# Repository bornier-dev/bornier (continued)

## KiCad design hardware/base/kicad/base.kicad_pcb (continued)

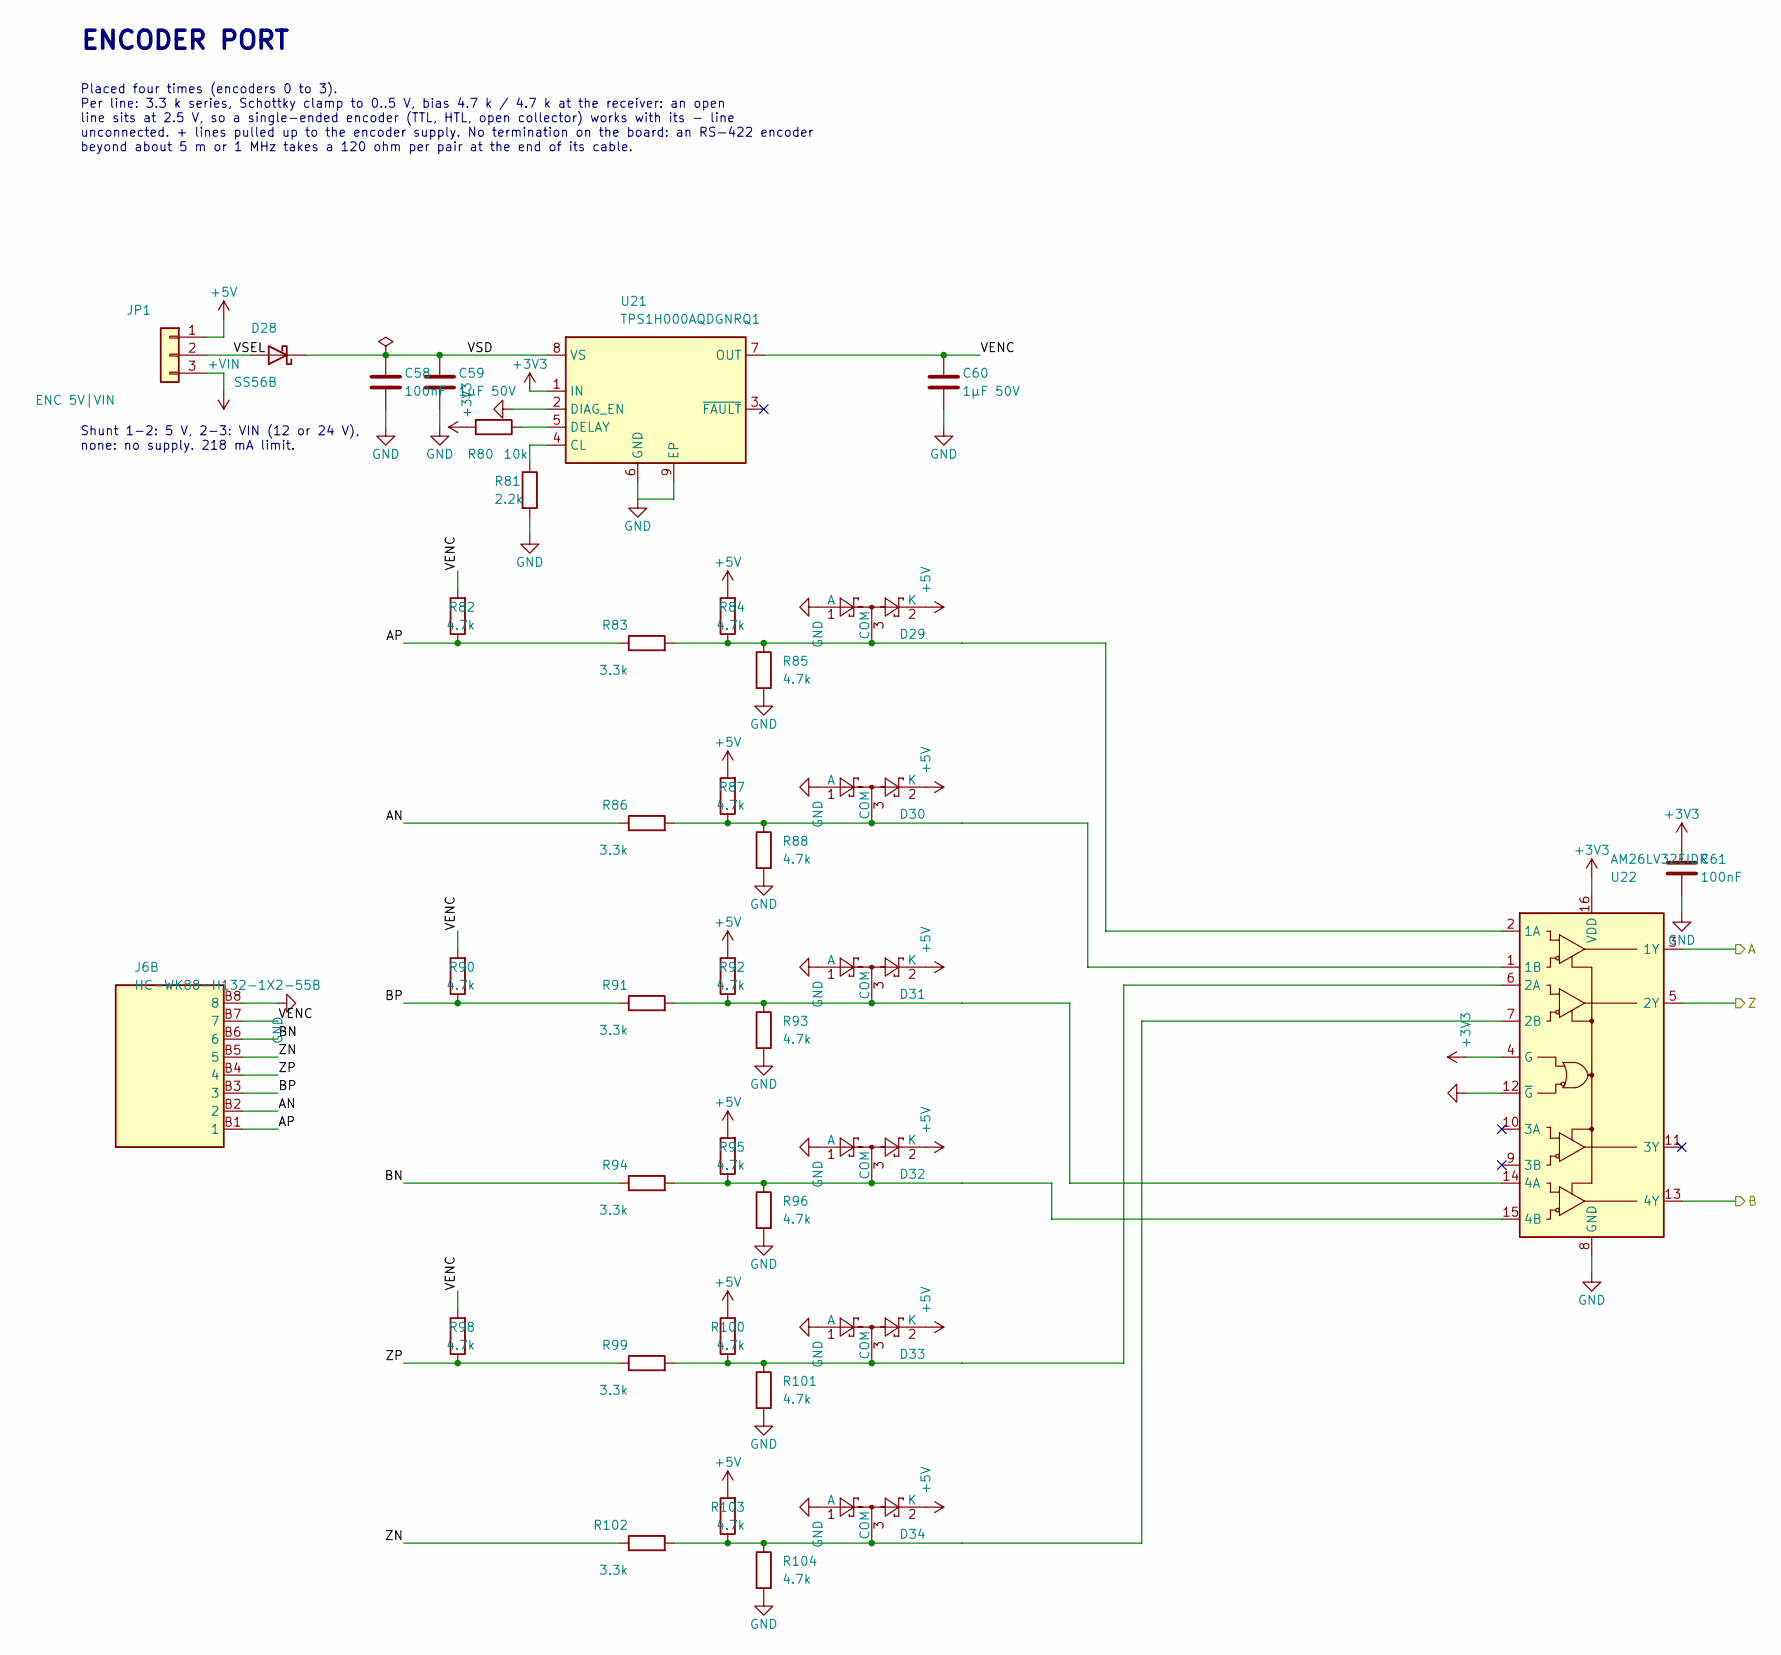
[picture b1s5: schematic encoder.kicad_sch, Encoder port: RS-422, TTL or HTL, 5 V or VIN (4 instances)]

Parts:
C58, C61: 100nF; C_0402_1005Metric; LCSC C307331
C59, C60: 1µF 50V; C_0603_1608Metric; LCSC C15849
D28: SS56B; D_SMB; LCSC C14651
D29, D30, D31, D32, D33, D34: BAT54S; SOT-23; LCSC C12765
J6: HC-WK88-H132-1X2-55B; RJ45x2_HongCheng_HC-WK88-H132-1X2-55B; LCSC C7501828
JP1: ENC 5V|VIN; PinHeader_1x03_P2.54mm_Vertical; LCSC C2937625
R80: 10k; R_0402_1005Metric; LCSC C25744
R81: 2.2k; R_0402_1005Metric; LCSC C25879
R82, R90, R98: 4.7k; R_1206_3216Metric; LCSC C17936
R83, R86, R91, R94, R99, R102: 3.3k; R_1206_3216Metric; LCSC C26032
R84, R85, R87, R88, R92, R93, R95, R96, R100, R101, R103, R104: 4.7k; R_0402_1005Metric; LCSC C25900
U21: TPS1H000AQDGNRQ1; HVSSOP-8-1EP_3x3mm_P0.65mm_EP1.57x1.89mm; LCSC C2653764
U22: AM26LV32EIDR; SOIC-16_3.9x9.9mm_P1.27mm; LCSC C527448

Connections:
+3V3: C61.1, R80.2, U21.1 (IN), U22.4 (G), U22.16 (VDD); also elsewhere on the board
+5V: D29.2 (K), D30.2 (K), D31.2 (K), D32.2 (K), D33.2 (K), D34.2 (K), JP1.1, R84.2, R87.2, R92.2, R95.2, R100.2, R103.2; also elsewhere on the board
+VIN: JP1.3; also elsewhere on the board
/Encoder 0/AN: J6.B2 (2), R86.1
/Encoder 0/AP: J6.B1 (1), R82.1, R83.1
/Encoder 0/BN: J6.B6 (6), R94.1
/Encoder 0/BP: J6.B3 (3), R90.1, R91.1
/Encoder 0/VENC: C60.1, J6.B7 (7), R82.2, R90.2, R98.2, U21.7 (OUT)
/Encoder 0/VSD: C58.1, C59.1, D28.1 (K), U21.8 (VS)
/Encoder 0/VSEL: D28.2 (A), JP1.2
/Encoder 0/ZN: J6.B5 (5), R102.1
/Encoder 0/ZP: J6.B4 (4), R98.1, R99.1
ENC0_A: U22.3 (1Y); also elsewhere on the board
ENC0_B: U22.13 (4Y); also elsewhere on the board
ENC0_Z: U22.5 (2Y); also elsewhere on the board
GND: C58.2, C59.2, C60.2, C61.2, D29.1 (A), D30.1 (A), D31.1 (A), D32.1 (A), D33.1 (A), D34.1 (A), J6.B8 (8), R81.2, R85.2, R88.2, R93.2, R96.2, R101.2, R104.2, U21.2 (DIAG_EN), U21.6 (GND), U21.9 (EP), U22.8 (GND), U22.12 (~G); also elsewhere on the board
unnamed: D29.3 (COM), R83.2, R84.1, R85.1, U22.2 (1A)
unnamed: D30.3 (COM), R86.2, R87.1, R88.1, U22.1 (1B)
unnamed: D31.3 (COM), R91.2, R92.1, R93.1, U22.14 (4A)
unnamed: D32.3 (COM), R94.2, R95.1, R96.1, U22.15 (4B)
unnamed: D33.3 (COM), R99.2, R100.1, R101.1, U22.6 (2A)
unnamed: D34.3 (COM), R102.2, R103.1, R104.1, U22.7 (2B)
unnamed: R81.1, U21.4 (CL)
unnamed: R80.1, U21.5 (DELAY)

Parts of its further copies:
C62, C65, C66, C69, C70, C73: 100nF; C_0402_1005Metric; LCSC C307331
C63, C64, C67, C68, C71, C72: 1µF 50V; C_0603_1608Metric; LCSC C15849
D35, D42, D49: SS56B; D_SMB; LCSC C14651
D36, D37, D38, D39, D40, D41, D43, D44, D45, D46, D47, D48, D50, D51, D52, D53, D54, D55: BAT54S; SOT-23; LCSC C12765
J7, J8, J9: HC-WK88-H132-1X2-55B; RJ45x2_HongCheng_HC-WK88-H132-1X2-55B; LCSC C7501828
JP2, JP3, JP4: ENC 5V|VIN; PinHeader_1x03_P2.54mm_Vertical; LCSC C2937625
R106, R132, R158: 10k; R_0402_1005Metric; LCSC C25744
R107, R133, R159: 2.2k; R_0402_1005Metric; LCSC C25879
R108, R116, R124, R134, R142, R150, R160, R168, R176: 4.7k; R_1206_3216Metric; LCSC C17936
R109, R112, R117, R120, R125, R128, R135, R138, R143, R146, R151, R154, R161, R164, R169, R172, R177, R180: 3.3k; R_1206_3216Metric; LCSC C26032
R110, R111, R113, R114, R118, R119, R121, R122, R126, R127, R129, R130, R136, R137, R139, R140, R144, R145, R147, R148, R152, R153, R155, R156, R162, R163, R165, R166, R170, R171, R173, R174, R178, R179, R181, R182: 4.7k; R_0402_1005Metric; LCSC C25900
U23, U25, U27: TPS1H000AQDGNRQ1; HVSSOP-8-1EP_3x3mm_P0.65mm_EP1.57x1.89mm; LCSC C2653764
U24, U26, U28: AM26LV32EIDR; SOIC-16_3.9x9.9mm_P1.27mm; LCSC C527448

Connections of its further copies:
+3V3: C65.1, C69.1, C73.1, R106.2, R132.2, R158.2, U23.1 (IN), U24.4 (G), U24.16 (VDD), U25.1 (IN), U26.4 (G), U26.16 (VDD), U27.1 (IN), U28.4 (G), U28.16 (VDD); also elsewhere on the board
+5V: D36.2 (K), D37.2 (K), D38.2 (K), D39.2 (K), D40.2 (K), D41.2 (K), D43.2 (K), D44.2 (K), D45.2 (K), D46.2 (K), D47.2 (K), D48.2 (K), D50.2 (K), D51.2 (K), D52.2 (K), D53.2 (K), D54.2 (K), D55.2 (K), JP2.1, JP3.1, JP4.1, R110.2, R113.2, R118.2, R121.2, R126.2, R129.2, R136.2, R139.2, R144.2, R147.2, R152.2, R155.2, R162.2, R165.2, R170.2, R173.2, R178.2, R181.2; also elsewhere on the board
+VIN: JP2.3, JP3.3, JP4.3; also elsewhere on the board
+VIN_OUT: J7.A7 (7), J8.A7 (7), J9.A7 (7); also elsewhere on the board
/Drive 1/ALM_IN: J7.A5 (5); also elsewhere on the board
/Drive 1/DIR_N: J7.A6 (6); also elsewhere on the board
/Drive 1/DIR_P: J7.A3 (3); also elsewhere on the board
/Drive 1/ENA_OUT: J7.A4 (4); also elsewhere on the board
/Drive 1/STEP_N: J7.A2 (2); also elsewhere on the board
/Drive 1/STEP_P: J7.A1 (1); also elsewhere on the board
/Drive 2/ALM_IN: J8.A5 (5); also elsewhere on the board
/Drive 2/DIR_N: J8.A6 (6); also elsewhere on the board
/Drive 2/DIR_P: J8.A3 (3); also elsewhere on the board
/Drive 2/ENA_OUT: J8.A4 (4); also elsewhere on the board
/Drive 2/STEP_N: J8.A2 (2); also elsewhere on the board
/Drive 2/STEP_P: J8.A1 (1); also elsewhere on the board
/Drive 3/ALM_IN: J9.A5 (5); also elsewhere on the board
/Drive 3/DIR_N: J9.A6 (6); also elsewhere on the board
/Drive 3/DIR_P: J9.A3 (3); also elsewhere on the board
/Drive 3/ENA_OUT: J9.A4 (4); also elsewhere on the board
/Drive 3/STEP_N: J9.A2 (2); also elsewhere on the board
/Drive 3/STEP_P: J9.A1 (1); also elsewhere on the board
/Encoder 1/AN: J7.B2 (2), R112.1
/Encoder 1/AP: J7.B1 (1), R108.1, R109.1
/Encoder 1/BN: J7.B6 (6), R120.1
/Encoder 1/BP: J7.B3 (3), R116.1, R117.1
/Encoder 1/VENC: C64.1, J7.B7 (7), R108.2, R116.2, R124.2, U23.7 (OUT)
/Encoder 1/VSD: C62.1, C63.1, D35.1 (K), U23.8 (VS)
/Encoder 1/VSEL: D35.2 (A), JP2.2
/Encoder 1/ZN: J7.B5 (5), R128.1
/Encoder 1/ZP: J7.B4 (4), R124.1, R125.1
/Encoder 2/AN: J8.B2 (2), R138.1
/Encoder 2/AP: J8.B1 (1), R134.1, R135.1
/Encoder 2/BN: J8.B6 (6), R146.1
/Encoder 2/BP: J8.B3 (3), R142.1, R143.1
/Encoder 2/VENC: C68.1, J8.B7 (7), R134.2, R142.2, R150.2, U25.7 (OUT)
/Encoder 2/VSD: C66.1, C67.1, D42.1 (K), U25.8 (VS)
/Encoder 2/VSEL: D42.2 (A), JP3.2
/Encoder 2/ZN: J8.B5 (5), R154.1
/Encoder 2/ZP: J8.B4 (4), R150.1, R151.1
/Encoder 3/AN: J9.B2 (2), R164.1
/Encoder 3/AP: J9.B1 (1), R160.1, R161.1
/Encoder 3/BN: J9.B6 (6), R172.1
/Encoder 3/BP: J9.B3 (3), R168.1, R169.1
/Encoder 3/VENC: C72.1, J9.B7 (7), R160.2, R168.2, R176.2, U27.7 (OUT)
/Encoder 3/VSD: C70.1, C71.1, D49.1 (K), U27.8 (VS)
/Encoder 3/VSEL: D49.2 (A), JP4.2
/Encoder 3/ZN: J9.B5 (5), R180.1
/Encoder 3/ZP: J9.B4 (4), R176.1, R177.1
CHASSIS: J7.SH, J8.SH, J9.SH; also elsewhere on the board
ENC1_A: U24.3 (1Y); also elsewhere on the board
ENC1_B: U24.13 (4Y); also elsewhere on the board
ENC1_Z: U24.5 (2Y); also elsewhere on the board
ENC2_A: U26.3 (1Y); also elsewhere on the board
ENC2_B: U26.13 (4Y); also elsewhere on the board
ENC2_Z: U26.5 (2Y); also elsewhere on the board
ENC3_A: U28.3 (1Y); also elsewhere on the board
ENC3_B: U28.13 (4Y); also elsewhere on the board
ENC3_Z: U28.5 (2Y); also elsewhere on the board
GND: C62.2, C63.2, C64.2, C65.2, C66.2, C67.2, C68.2, C69.2, C70.2, C71.2, C72.2, C73.2, D36.1 (A), D37.1 (A), D38.1 (A), D39.1 (A), D40.1 (A), D41.1 (A), D43.1 (A), D44.1 (A), D45.1 (A), D46.1 (A), D47.1 (A), D48.1 (A), D50.1 (A), D51.1 (A), D52.1 (A), D53.1 (A), D54.1 (A), D55.1 (A), J7.A8 (8), J7.B8 (8), J8.A8 (8), J8.B8 (8), J9.A8 (8), J9.B8 (8), R107.2, R111.2, R114.2, R119.2, R122.2, R127.2, R130.2, R133.2, R137.2, R140.2, R145.2, R148.2, R153.2, R156.2, R159.2, R163.2, R166.2, R171.2, R174.2, R179.2, R182.2, U23.2 (DIAG_EN), U23.6 (GND), U23.9 (EP), U24.8 (GND), U24.12 (~G), U25.2 (DIAG_EN), U25.6 (GND), U25.9 (EP), U26.8 (GND), U26.12 (~G), U27.2 (DIAG_EN), U27.6 (GND), U27.9 (EP), U28.8 (GND), U28.12 (~G); also elsewhere on the board
unnamed: D36.3 (COM), R109.2, R110.1, R111.1, U24.2 (1A)
unnamed: D37.3 (COM), R112.2, R113.1, R114.1, U24.1 (1B)
unnamed: D38.3 (COM), R117.2, R118.1, R119.1, U24.14 (4A)
unnamed: D39.3 (COM), R120.2, R121.1, R122.1, U24.15 (4B)
unnamed: D40.3 (COM), R125.2, R126.1, R127.1, U24.6 (2A)
unnamed: D41.3 (COM), R128.2, R129.1, R130.1, U24.7 (2B)
unnamed: D43.3 (COM), R135.2, R136.1, R137.1, U26.2 (1A)
unnamed: D44.3 (COM), R138.2, R139.1, R140.1, U26.1 (1B)
unnamed: D45.3 (COM), R143.2, R144.1, R145.1, U26.14 (4A)
unnamed: D46.3 (COM), R146.2, R147.1, R148.1, U26.15 (4B)
unnamed: D47.3 (COM), R151.2, R152.1, R153.1, U26.6 (2A)
unnamed: D48.3 (COM), R154.2, R155.1, R156.1, U26.7 (2B)
unnamed: D50.3 (COM), R161.2, R162.1, R163.1, U28.2 (1A)
unnamed: D51.3 (COM), R164.2, R165.1, R166.1, U28.1 (1B)
unnamed: D52.3 (COM), R169.2, R170.1, R171.1, U28.14 (4A)
unnamed: D53.3 (COM), R172.2, R173.1, R174.1, U28.15 (4B)
unnamed: D54.3 (COM), R177.2, R178.1, R179.1, U28.6 (2A)
unnamed: D55.3 (COM), R180.2, R181.1, R182.1, U28.7 (2B)
unnamed: R107.1, U23.4 (CL)
unnamed: R106.1, U23.5 (DELAY)
unnamed: R133.1, U25.4 (CL)
unnamed: R132.1, U25.5 (DELAY)
unnamed: R159.1, U27.4 (CL)
unnamed: R158.1, U27.5 (DELAY)

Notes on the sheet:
ENCODER PORT
Placed four times (encoders 0 to 3). Per line: 3.3 k series, Schottky clamp to 0..5 V, bias 4.7 k / 4.7 k at the receiver: an open line sits at 2.5 V, so a single-ended encoder (TTL, HTL, open collector) works with its - line unconnected. + lines pulled up to the encoder supply. No termination on t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
Shunt 1-2: 5 V, 2-3: VIN (12 or 24 V), none: no supply. 218 mA limit.

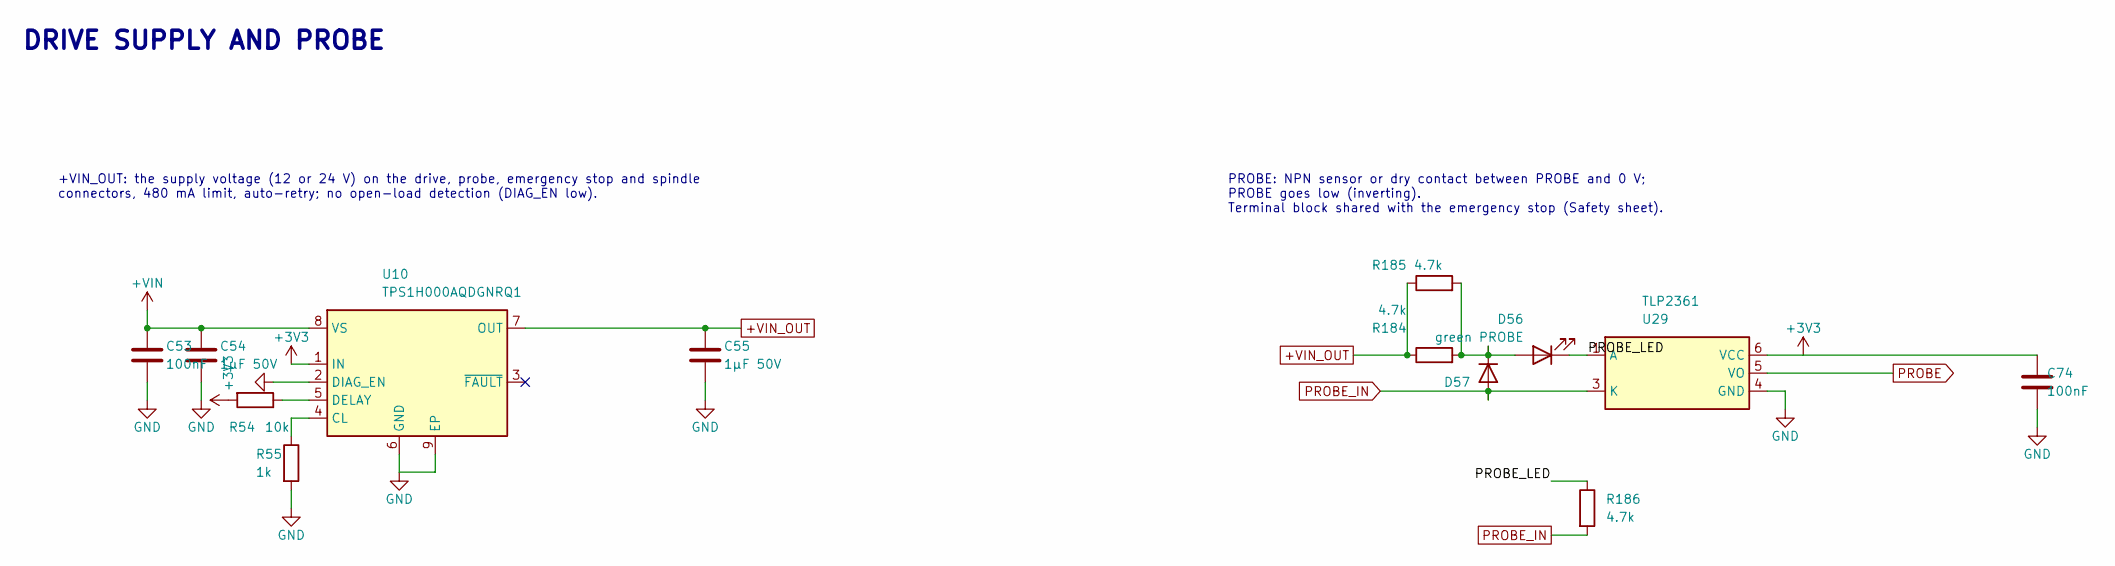
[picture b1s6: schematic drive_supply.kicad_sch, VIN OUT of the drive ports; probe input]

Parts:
C53, C74: 100nF; C_0402_1005Metric; LCSC C307331
C54, C55: 1µF 50V; C_0603_1608Metric; LCSC C15849
D56: green PROBE; LED_0603_1608Metric; LCSC C2289
D57: 1N4148WS; D_SOD-323; LCSC C2128
R54: 10k; R_0402_1005Metric; LCSC C25744
R55: 1k; R_0402_1005Metric; LCSC C11702
R184, R185: 4.7k; R_1206_3216Metric; LCSC C17936
R186: 4.7k; R_0402_1005Metric; LCSC C25900
U10: TPS1H000AQDGNRQ1; HVSSOP-8-1EP_3x3mm_P0.65mm_EP1.57x1.89mm; LCSC C2653764
U29: TLP2361; SO-5-6_4.55x3.7mm_P1.27mm; LCSC C107626

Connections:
+3V3: C74.1, R54.2, U10.1 (IN), U29.6 (VCC); also elsewhere on the board
+VIN: C53.1, C54.1, U10.8 (VS); also elsewhere on the board
+VIN_OUT: C55.1, R184.1, R185.1, U10.7 (OUT); also elsewhere on the board
/Drive supply and probe/PROBE_LED: D56.1 (K), R186.1, U29.1 (A)
GND: C53.2, C54.2, C55.2, C74.2, R55.2, U10.2 (DIAG_EN), U10.6 (GND), U10.9 (EP), U29.4 (GND); also elsewhere on the board
unnamed: D56.2 (A), D57.1 (K), R184.2, R185.2
unnamed: R55.1, U10.4 (CL)
unnamed: R54.1, U10.5 (DELAY)
PROBE: U29.5 (VO); also elsewhere on the board
PROBE_IN: D57.2 (A), R186.2, U29.3 (K); also elsewhere on the board

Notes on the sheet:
DRIVE SUPPLY AND PROBE
+VIN_OUT: the supply voltage (12 or 24 V) on the drive, probe, emergency stop and spindle connectors, 480 mA limit, auto-retry; no open-load detection (DIAG_EN low).
PROBE: NPN sensor or dry contact between PROBE and 0 V; PROBE goes low (inverting). Terminal block shared with the emergency stop (Safety sheet).

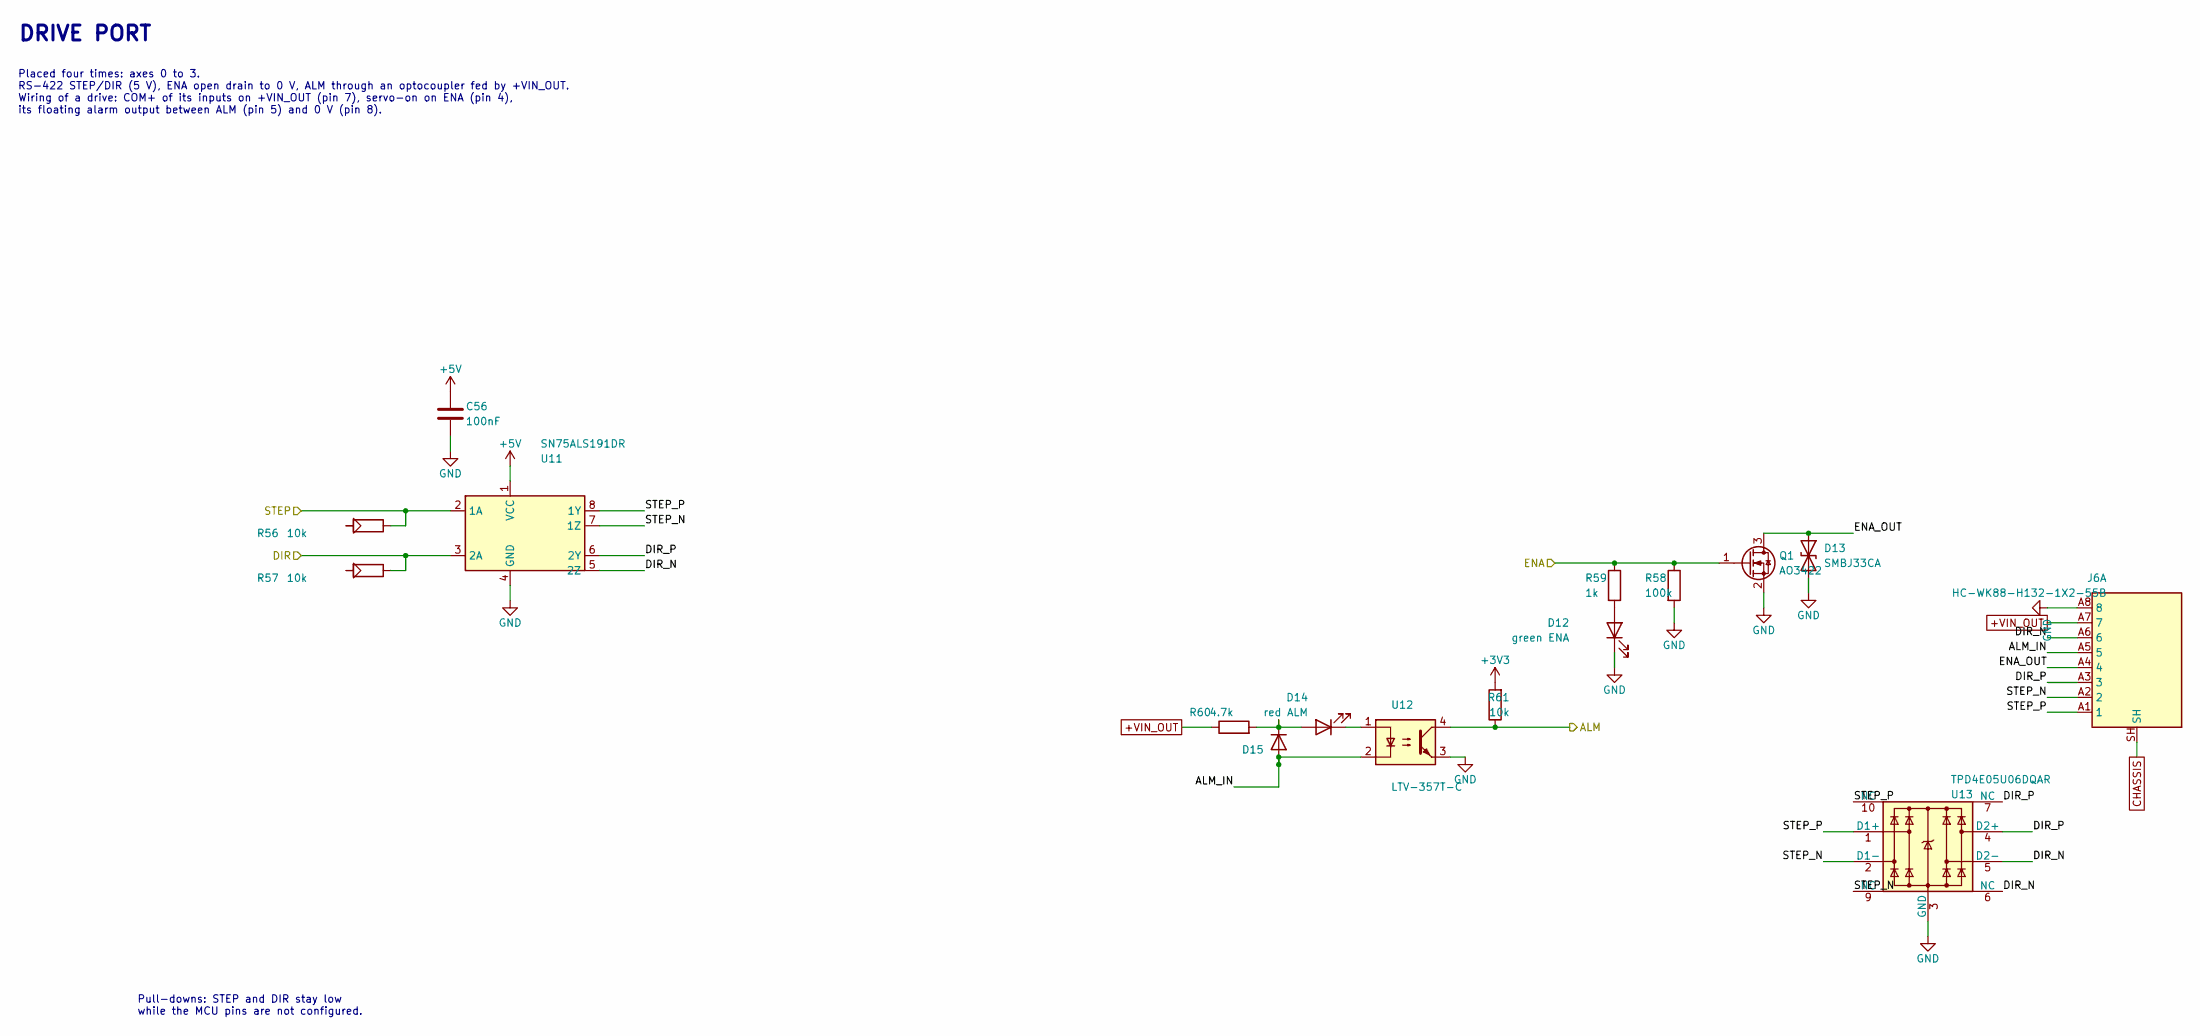
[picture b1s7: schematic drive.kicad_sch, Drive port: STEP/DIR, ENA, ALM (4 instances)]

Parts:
C56: 100nF; C_0402_1005Metric; LCSC C307331
D12: green ENA; LED_0603_1608Metric; LCSC C2289
D13: SMBJ33CA; D_SMB; LCSC C78420
D14: red ALM; LED_0603_1608Metric; LCSC C2286
D15: 1N4148WS; D_SOD-323; LCSC C2128
J6: HC-WK88-H132-1X2-55B; RJ45x2_HongCheng_HC-WK88-H132-1X2-55B; LCSC C7501828
Q1: AO3422; SOT-23; LCSC C37130
R56, R57, R61: 10k; R_0402_1005Metric; LCSC C25744
R58: 100k; R_0402_1005Metric; LCSC C25741
R59: 1k; R_0402_1005Metric; LCSC C11702
R60: 4.7k; R_1206_3216Metric; LCSC C17936
U11: SN75ALS191DR; SOIC-8_3.9x4.9mm_P1.27mm; LCSC C2871261
U12: LTV-357T-C; SO-4_4.4x3.6mm_P2.54mm; LCSC C119091
U13: TPD4E05U06DQAR; USON-10_2.5x1.0mm_P0.5mm; LCSC C138714

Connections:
+3V3: R61.2; also elsewhere on the board
+5V: C56.1, U11.1 (VCC); also elsewhere on the board
+VIN_OUT: J6.A7 (7), R60.1; also elsewhere on the board
/Drive 0/ALM_IN: D15.2 (A), J6.A5 (5), U12.2
/Drive 0/DIR_N: J6.A6 (6), U11.5 (2Z), U13.5 (D2-), U13.6 (NC)
/Drive 0/DIR_P: J6.A3 (3), U11.6 (2Y), U13.4 (D2+), U13.7 (NC)
/Drive 0/ENA_OUT: D13.1 (A1), J6.A4 (4), Q1.3 (D)
/Drive 0/STEP_N: J6.A2 (2), U11.7 (1Z), U13.2 (D1-), U13.9 (NC)
/Drive 0/STEP_P: J6.A1 (1), U11.8 (1Y), U13.1 (D1+), U13.10 (NC)
ALM0: R61.1, U12.4; also elsewhere on the board
CHASSIS: J6.SH; also elsewhere on the board
DIR0: R57.1, U11.3 (2A); also elsewhere on the board
ENA0: Q1.1 (G), R58.1, R59.1; also elsewhere on the board
GND: C56.2, D12.1 (K), D13.2 (A2), J6.A8 (8), Q1.2 (S), R56.2, R57.2, R58.2, U11.4 (GND), U12.3, U13.3 (GND), U13.8 (GND); also elsewhere on the board
unnamed: D12.2 (A), R59.2
unnamed: D14.2 (A), D15.1 (K), R60.2
unnamed: D14.1 (K), U12.1
STEP0: R56.1, U11.2 (1A); also elsewhere on the board

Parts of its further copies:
C57, C320, C321: 100nF; C_0402_1005Metric; LCSC C307331
D16, D20, D24: green ENA; LED_0603_1608Metric; LCSC C2289
D17, D21, D25: SMBJ33CA; D_SMB; LCSC C78420
D18, D22, D26: red ALM; LED_0603_1608Metric; LCSC C2286
D19, D23, D27: 1N4148WS; D_SOD-323; LCSC C2128
J7, J8, J9: HC-WK88-H132-1X2-55B; RJ45x2_HongCheng_HC-WK88-H132-1X2-55B; LCSC C7501828
Q2, Q3, Q4: AO3422; SOT-23; LCSC C37130
R62, R63, R67, R68, R69, R73, R74, R75, R79: 10k; R_0402_1005Metric; LCSC C25744
R64, R70, R76: 100k; R_0402_1005Metric; LCSC C25741
R65, R71, R77: 1k; R_0402_1005Metric; LCSC C11702
R66, R72, R78: 4.7k; R_1206_3216Metric; LCSC C17936
U14, U17, U19: LTV-357T-C; SO-4_4.4x3.6mm_P2.54mm; LCSC C119091
U15, U18, U20: TPD4E05U06DQAR; USON-10_2.5x1.0mm_P0.5mm; LCSC C138714
U16, U300, U301: SN75ALS191DR; SOIC-8_3.9x4.9mm_P1.27mm; LCSC C2871261

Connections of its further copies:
+3V3: R67.2, R73.2, R79.2; also elsewhere on the board
+5V: C57.1, C320.1, C321.1, U16.1 (VCC), U300.1 (VCC), U301.1 (VCC); also elsewhere on the board
+VIN_OUT: J7.A7 (7), J8.A7 (7), J9.A7 (7), R66.1, R72.1, R78.1; also elsewhere on the board
/Drive 1/ALM_IN: D19.2 (A), J7.A5 (5), U14.2
/Drive 1/DIR_N: J7.A6 (6), U15.5 (D2-), U15.6 (NC), U300.5 (2Z)
/Drive 1/DIR_P: J7.A3 (3), U15.4 (D2+), U15.7 (NC), U300.6 (2Y)
/Drive 1/ENA_OUT: D17.1 (A1), J7.A4 (4), Q2.3 (D)
/Drive 1/STEP_N: J7.A2 (2), U15.2 (D1-), U15.9 (NC), U300.7 (1Z)
/Drive 1/STEP_P: J7.A1 (1), U15.1 (D1+), U15.10 (NC), U300.8 (1Y)
/Drive 2/ALM_IN: D23.2 (A), J8.A5 (5), U17.2
/Drive 2/DIR_N: J8.A6 (6), U16.5 (2Z), U18.5 (D2-), U18.6 (NC)
/Drive 2/DIR_P: J8.A3 (3), U16.6 (2Y), U18.4 (D2+), U18.7 (NC)
/Drive 2/ENA_OUT: D21.1 (A1), J8.A4 (4), Q3.3 (D)
/Drive 2/STEP_N: J8.A2 (2), U16.7 (1Z), U18.2 (D1-), U18.9 (NC)
/Drive 2/STEP_P: J8.A1 (1), U16.8 (1Y), U18.1 (D1+), U18.10 (NC)
/Drive 3/ALM_IN: D27.2 (A), J9.A5 (5), U19.2
/Drive 3/DIR_N: J9.A6 (6), U20.5 (D2-), U20.6 (NC), U301.5 (2Z)
/Drive 3/DIR_P: J9.A3 (3), U20.4 (D2+), U20.7 (NC), U301.6 (2Y)
/Drive 3/ENA_OUT: D25.1 (A1), J9.A4 (4), Q4.3 (D)
/Drive 3/STEP_N: J9.A2 (2), U20.2 (D1-), U20.9 (NC), U301.7 (1Z)
/Drive 3/STEP_P: J9.A1 (1), U20.1 (D1+), U20.10 (NC), U301.8 (1Y)
/Encoder 1/AN: J7.B2 (2); also elsewhere on the board
/Encoder 1/AP: J7.B1 (1); also elsewhere on the board
/Encoder 1/BN: J7.B6 (6); also elsewhere on the board
/Encoder 1/BP: J7.B3 (3); also elsewhere on the board
/Encoder 1/VENC: J7.B7 (7); also elsewhere on the board
/Encoder 1/ZN: J7.B5 (5); also elsewhere on the board
/Encoder 1/ZP: J7.B4 (4); also elsewhere on the board
/Encoder 2/AN: J8.B2 (2); also elsewhere on the board
/Encoder 2/AP: J8.B1 (1); also elsewhere on the board
/Encoder 2/BN: J8.B6 (6); also elsewhere on the board
/Encoder 2/BP: J8.B3 (3); also elsewhere on the board
/Encoder 2/VENC: J8.B7 (7); also elsewhere on the board
/Encoder 2/ZN: J8.B5 (5); also elsewhere on the board
/Encoder 2/ZP: J8.B4 (4); also elsewhere on the board
/Encoder 3/AN: J9.B2 (2); also elsewhere on the board
/Encoder 3/AP: J9.B1 (1); also elsewhere on the board
/Encoder 3/BN: J9.B6 (6); also elsewhere on the board
/Encoder 3/BP: J9.B3 (3); also elsewhere on the board
/Encoder 3/VENC: J9.B7 (7); also elsewhere on the board
/Encoder 3/ZN: J9.B5 (5); also elsewhere on the board
/Encoder 3/ZP: J9.B4 (4); also elsewhere on the board
ALM1: R67.1, U14.4; also elsewhere on the board
ALM2: R73.1, U17.4; also elsewhere on the board
ALM3: R79.1, U19.4; also elsewhere on the board
CHASSIS: J7.SH, J8.SH, J9.SH; also elsewhere on the board
DIR1: R63.1, U300.3 (2A); also elsewhere on the board
DIR2: R69.1, U16.3 (2A); also elsewhere on the board
DIR3: R75.1, U301.3 (2A); also elsewhere on the board
ENA1: Q2.1 (G), R64.1, R65.1; also elsewhere on the board
ENA2: Q3.1 (G), R70.1, R71.1; also elsewhere on the board
ENA3: Q4.1 (G), R76.1, R77.1; also elsewhere on the board
GND: C57.2, C320.2, C321.2, D16.1 (K), D17.2 (A2), D20.1 (K), D21.2 (A2), D24.1 (K), D25.2 (A2), J7.A8 (8), J7.B8 (8), J8.A8 (8), J8.B8 (8), J9.A8 (8), J9.B8 (8), Q2.2 (S), Q3.2 (S), Q4.2 (S), R62.2, R63.2, R64.2, R68.2, R69.2, R70.2, R74.2, R75.2, R76.2, U14.3, U15.3 (GND), U15.8 (GND), U16.4 (GND), U17.3, U18.3 (GND), U18.8 (GND), U19.3, U20.3 (GND), U20.8 (GND), U300.4 (GND), U301.4 (GND); also elsewhere on the board
unnamed: D16.2 (A), R65.2
unnamed: D18.2 (A), D19.1 (K), R66.2
unnamed: D18.1 (K), U14.1
unnamed: D20.2 (A), R71.2
unnamed: D22.2 (A), D23.1 (K), R72.2
unnamed: D22.1 (K), U17.1
unnamed: D24.2 (A), R77.2
unnamed: D26.2 (A), D27.1 (K), R78.2
unnamed: D26.1 (K), U19.1
STEP1: R62.1, U300.2 (1A); also elsewhere on the board
STEP2: R68.1, U16.2 (1A); also elsewhere on the board
STEP3: R74.1, U301.2 (1A); also elsewhere on the board

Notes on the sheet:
DRIVE PORT
Placed four times: axes 0 to 3. RS-422 STEP/DIR (5 V), ENA open drain to 0 V, ALM through an optocoupler fed by +VIN_OUT. Wiring of a drive: COM+ of its inputs on +VIN_OUT (pin 7), servo-on on ENA (pin 4), its floating alarm output between ALM (pin 5) and 0 V (pin 8).
Pull-downs: STEP and DIR stay low while the MCU pins are not configured.
